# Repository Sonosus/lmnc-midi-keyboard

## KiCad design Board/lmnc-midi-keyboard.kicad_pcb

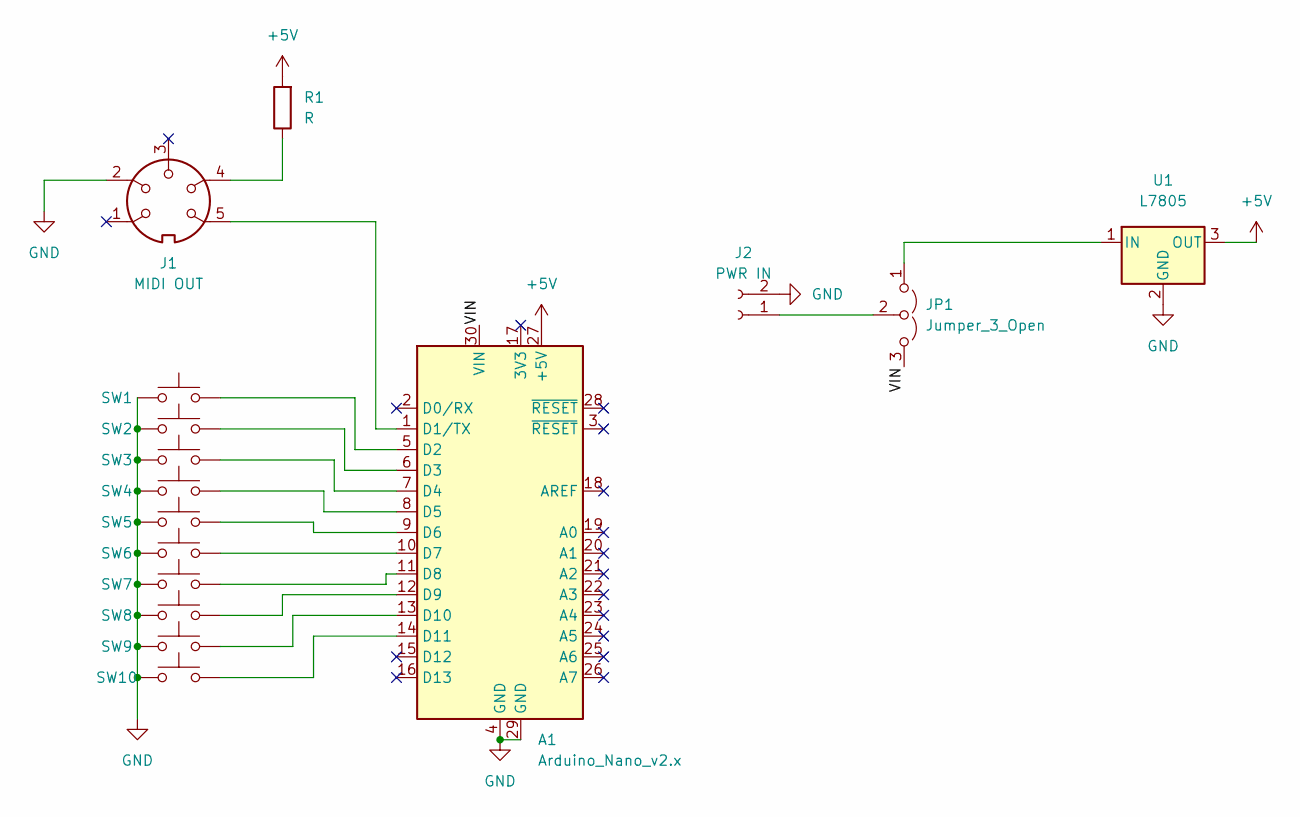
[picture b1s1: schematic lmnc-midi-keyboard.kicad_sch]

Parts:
A1: Arduino_Nano_v2.x; Arduino_Nano
J1: MIDI OUT; DIN5
J2: PWR IN; BarrelJack_Horizontal
JP1: Jumper_3_Open; SolderJumper-3_P1.3mm_Open_RoundedPad1.0x1.5mm_NumberLabels
R1: R; R_Axial_DIN0207_L6.3mm_D2.5mm_P7.62mm_Horizontal
SW1, SW2, SW3, SW4, SW5, SW6, SW7, SW8, SW9, SW10: SW_Push; SW_PUSH_6mm
U1: L7805; TO-220-3_Vertical

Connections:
+5V: A1.27 (+5V), R1.2, U1.3 (OUT)
/VIN: A1.30 (VIN), JP1.3 (B)
GND: A1.4 (GND), A1.29 (GND), J1.2, J2.2, SW1.1, SW2.1, SW3.1, SW4.1, SW5.1, SW6.1, SW7.1, SW8.1, SW9.1, SW10.1, U1.2 (GND)
unnamed: A1.1 (D1/TX), J1.5
unnamed: A1.5 (D2), SW1.2
unnamed: A1.6 (D3), SW2.2
unnamed: A1.7 (D4), SW3.2
unnamed: A1.8 (D5), SW4.2
unnamed: A1.9 (D6), SW5.2
unnamed: A1.10 (D7), SW6.2
unnamed: A1.11 (D8), SW7.2
unnamed: A1.12 (D9), SW8.2
unnamed: A1.13 (D10), SW9.2
unnamed: A1.14 (D11), SW10.2
unnamed: J1.4, R1.1
unnamed: J2.1, JP1.2 (C)
unnamed: JP1.1 (A), U1.1 (IN)

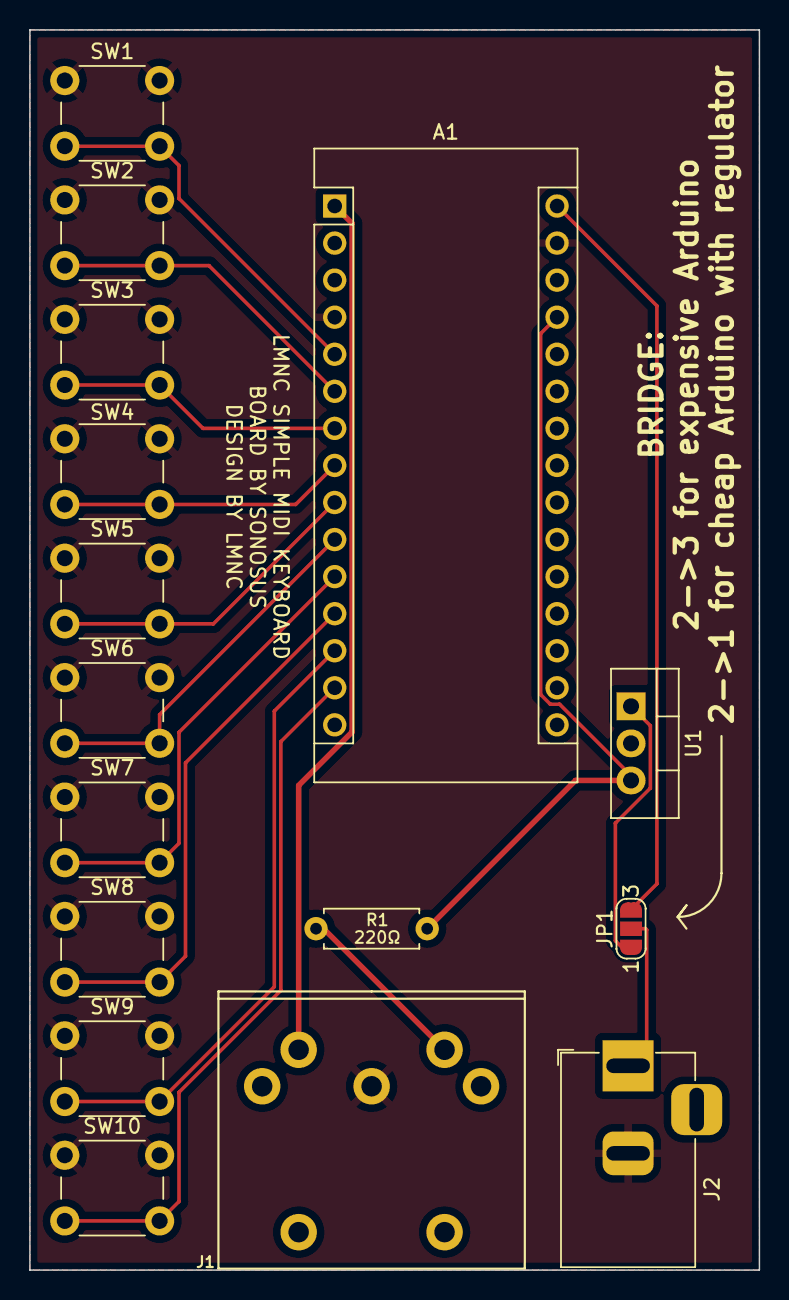
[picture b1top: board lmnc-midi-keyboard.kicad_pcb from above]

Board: 2 copper layers, 50.0 x 85.0 mm, 16 parts (0 on the bottom side), 17 nets.

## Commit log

2022-01-11 add board file
